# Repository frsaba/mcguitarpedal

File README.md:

# Teensy 4.1 Guitar Effects Pedal

#### Custom dual-layer PCB design:
- LM4562 based preamplifier stage with adjustable gain (1-20x) and 3-way attenuation switch for line-level compatibility
- 8+2+1 programmable buttons (up to 8 pushbuttons, 2 footswitches, 1 true bypass switch)
- 3 potentiometers (preamp gain + 2 programmable)
- 3 encoders (3 headers, but 2 are in use for now)
- 8 programmable LEDs
- 9V barrel jack input or USB power

[PCB design, front side](https://github.com/user-attachments/files/19494445/pcb_front.pdf)

[PCB design, back side](https://github.com/user-attachments/files/19494519/pcb_back.pdf)

## Hardware
- [Teensy 4.1](https://www.pjrc.com/store/teensy41.html)
- [Teensy Audio Adaptor board](https://www.pjrc.com/store/teensy3_audio.html)
- ILI9488 LCD panel (backlight brightness adjustable with PWM)

## Software

- C++ with PlatformIO
- [Teensy Audio Library](https://github.com/PaulStoffregen/Audio)
- UI made with [LVGL](https://lvgl.io)
- 5 implemented effects (more to come):
  - Chorus
  - Flanger
  - Tremolo
  - Delay
  - Reverb

Each effect can be separately toggled on/off and mixed with the dry/wet parameter. The effect parameters can be adjusted to tune the sound.

#### Misc. features
- Tuner mode
- Adjustable LED and display brightness
- Bypass switch
- Signal level feedback LED
- USB audio device for recording
- Headphone monitor out via Audio Board

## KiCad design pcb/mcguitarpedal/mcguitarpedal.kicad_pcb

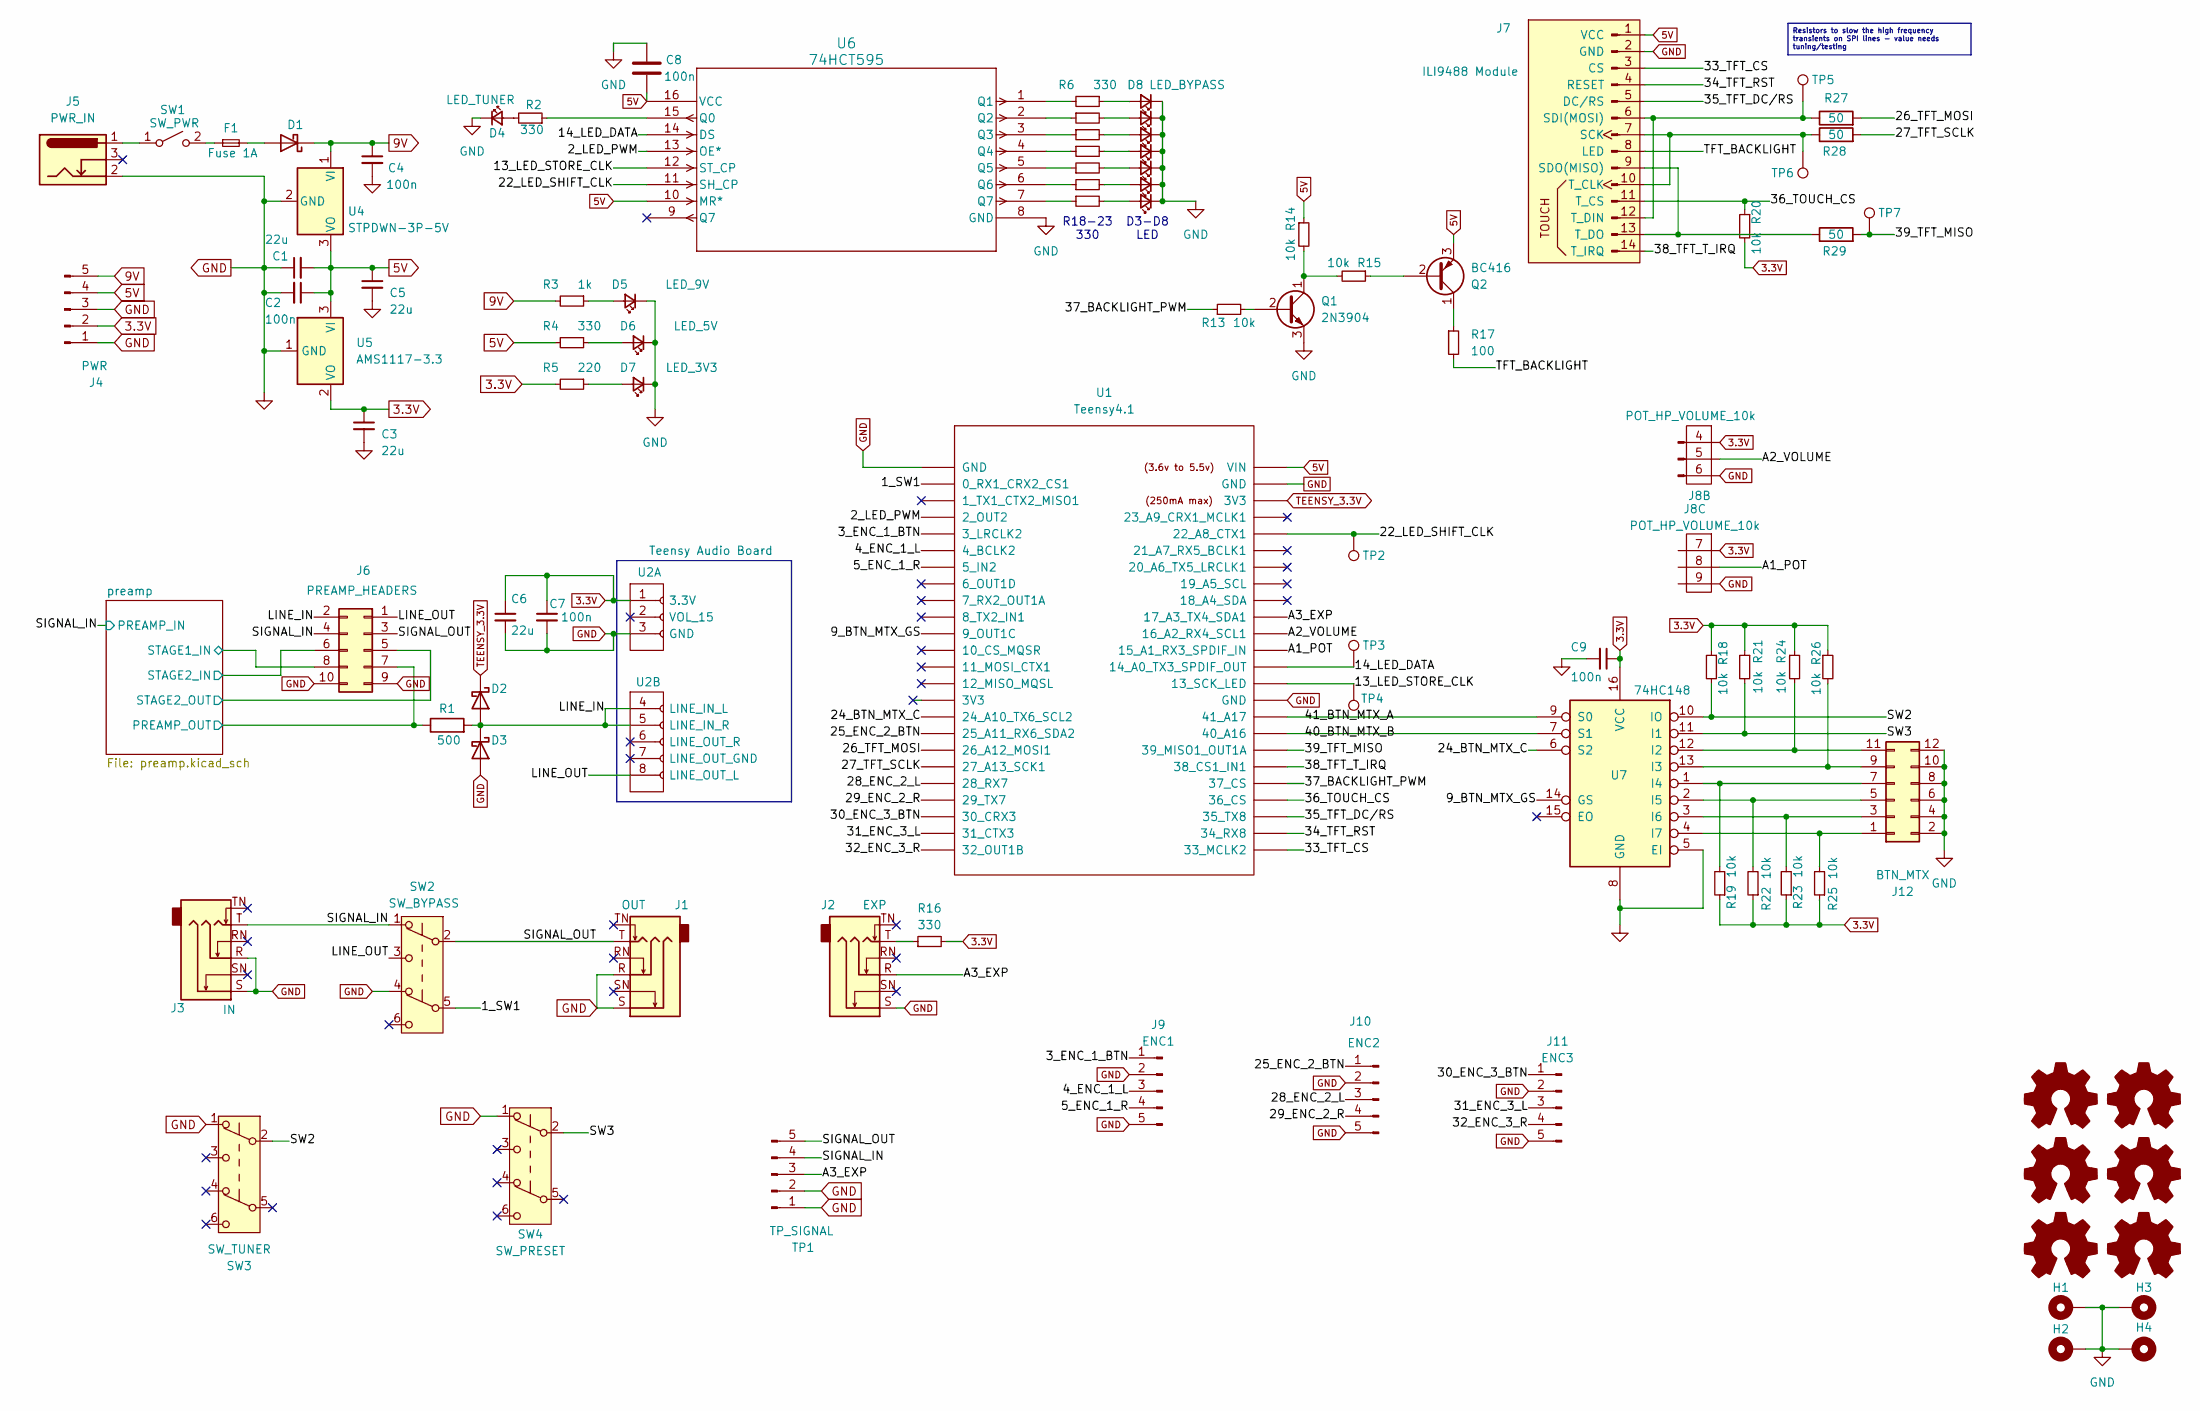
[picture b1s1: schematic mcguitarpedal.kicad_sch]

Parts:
C1, C3, C5, C6: 22u; CP_EIA-3216-18_Kemet-A_Pad1.58x1.35mm_HandSolder
C2, C4, C8, C9: 100n; C_1206_3216Metric_Pad1.33x1.80mm_HandSolder
C7: 100n; C_Rect_L7.2mm_W2.5mm_P5.00mm_FKS2_FKP2_MKS2_MKP2
D1, D2, D3: D_Schottky; D_DO-41_SOD81_P10.16mm_Horizontal
D4: LED_TUNER; LED_D5.0mm
D5: LED_9V; LED_D3.0mm
D6: LED_5V; LED_D3.0mm
D7: LED_3V3; LED_D3.0mm
D8: LED_BYPASS; LED_D5.0mm
D9: LED_STATUS; LED_D5.0mm
D10, D11, D12, D13, D14: LED; LED_D3.0mm
ENC1, ENC2, ENC3: Logo_Open_Hardware_Small; Floating Encoder
F1: Fuse 1A; Fuse_Littelfuse_395Series
H1, H2, H3, H4: MountingHole_Pad; MountingHole_2.2mm_M2_Pad
J1: OUT; Jack_6.35mm_Neutrik_NMJ6HCD2_Horizontal_3D_MODEL
J2: EXP; Jack_6.35mm_Neutrik_NMJ6HCD2_Horizontal_3D_MODEL
J3: IN; Jack_6.35mm_Neutrik_NMJ6HCD2_Horizontal_3D_MODEL
J4: PWR; PinHeader_1x05_P2.54mm_Vertical
J5: PWR_IN; BarrelJack_Kycon_KLDX-0202-xC_Horizontal
J6: PREAMP_HEADERS
J7: ILI9488 Module; ILI9488
J8: POT_HP_VOLUME_10k; POTS_HEADER
J9: ENC1; Encoder_headers
J10: ENC2; Encoder_headers
J11: ENC3; Encoder_headers
J12: BTN_MTX; PinHeader_2x06_P2.54mm_Vertical
POT1, POT2, POT3: Logo_Open_Hardware_Small; Floating Potentiometer
Q1: 2N3904; TO-92_Inline
Q2: BC416; TO-92_Inline
R1: 500; R_Axial_DIN0207_L6.3mm_D2.5mm_P7.62mm_Horizontal
R2, R4, R6, R7, R8, R9, R10, R11, R12, R16: 330; R_1206_3216Metric_Pad1.30x1.75mm_HandSolder
R3: 1k; R_Axial_DIN0207_L6.3mm_D2.5mm_P7.62mm_Horizontal
R5: 220; R_Axial_DIN0207_L6.3mm_D2.5mm_P7.62mm_Horizontal
R13, R14, R15, R18, R19, R20, R21, R22, R23, R24, R25, R26: 10k; R_1206_3216Metric_Pad1.30x1.75mm_HandSolder
R17: 100; R_Axial_DIN0207_L6.3mm_D2.5mm_P7.62mm_Horizontal
R27, R28, R29: 50; R_1206_3216Metric_Pad1.30x1.75mm_HandSolder
SW1: SW_PWR; PinHeader_1x02_P2.54mm_Vertical
SW2: SW_BYPASS; SW_PUSH_DPDT
SW3: SW_TUNER; SW_PUSH_DPDT
SW4: SW_PRESET; SW_PUSH_DPDT
TP1: TP_SIGNAL; PinHeader_1x05_P2.54mm_Vertical
TP2: SHIFT_CLK; TestPoint_Loop_D1.80mm_Drill1.0mm_Beaded
TP3: TP_LED_DATA; TestPoint_Loop_D1.80mm_Drill1.0mm_Beaded
TP4: TP_STORE_CLK; TestPoint_Loop_D1.80mm_Drill1.0mm_Beaded
TP5: TP_MOSI; TestPoint_Loop_D1.80mm_Drill1.0mm_Beaded
TP6: TP_SCLK; TestPoint_Loop_D1.80mm_Drill1.0mm_Beaded
TP7: TP_MISO; TestPoint_Loop_D1.80mm_Drill1.0mm_Beaded
U1: Teensy4.1; Teensy 4.1 with audio board
U2: Teensy Audio Board; 4.0audioshield
U4: STPDWN-3P-5V
U5: AMS1117-3.3; SOT-223-3_TabPin2
U6: 74HCT595; SOT109-1_NEX
U7: 74HC148; DIP16_300_TEX

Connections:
3.3V: C3.1, C6.1, C7.1, C9.1, J4.2, J8.4, J8.7, R5.2, R16.2, R18.1, R19.1, R20.2, R21.1, R22.1, R23.1, R24.1, R25.1, R26.1, U2.1 (3.3V), U5.2 (VO), U7.16 (VCC)
5V: C1.2, C2.1, C5.1, C8.2, J4.4, J7.1 (VCC), Q2.3 (E), R4.2, R14.1, U1.48 (VIN), U4.3 (VO), U5.3 (VI), U6.10 (MR*), U6.16 (VCC)
9V: C4.1, D1.1 (K), J4.5, R3.2, U4.1 (VI); also elsewhere on the board
/1_SW1: SW2.5 (B), U1.2 (0_RX1_CRX2_CS1)
/2_LED_PWM: U1.4 (2_OUT2), U6.13 (OE*)
/3_ENC_1_BTN: J9.1, U1.5 (3_LRCLK2)
/4_ENC_1_L: J9.3, U1.6 (4_BCLK2)
/5_ENC_1_R: J9.4, U1.7 (5_IN2)
/9_BTN_MTX_GS: U1.11 (9_OUT1C), U7.14 (GS)
/13_LED_STORE_CLK: TP4.1, U1.35 (13_SCK_LED), U6.12 (ST_CP)
/14_LED_DATA: TP3.1, U1.36 (14_A0_TX3_SPDIF_OUT), U6.14 (DS)
/22_LED_SHIFT_CLK: TP2.1, U1.44 (22_A8_CTX1), U6.11 (SH_CP)
/24_BTN_MTX_C: U1.16 (24_A10_TX6_SCL2), U7.6 (S2)
/25_ENC_2_BTN: J10.1, U1.17 (25_A11_RX6_SDA2)
/26_TFT_MOSI: R27.2, U1.18 (26_A12_MOSI1)
/27_TFT_SCLK: R28.2, U1.19 (27_A13_SCK1)
/28_ENC_2_L: J10.3, U1.20 (28_RX7)
/29_ENC_2_R: J10.4, U1.21 (29_TX7)
/30_ENC_3_BTN: J11.1, U1.22 (30_CRX3)
/31_ENC_3_L: J11.3, U1.23 (31_CTX3)
/32_ENC_3_R: J11.4, U1.24 (32_OUT1B)
/33_TFT_CS: J7.3 (CS), U1.25 (33_MCLK2)
/34_TFT_RST: J7.4 (RESET), U1.26 (34_RX8)
/35_TFT_DC/RS: J7.5 (DC/RS), U1.27 (35_TX8)
/36_TOUCH_CS: J7.11 (T_CS), R20.1, U1.28 (36_CS)
/37_BACKLIGHT_PWM: R13.1, U1.29 (37_CS)
/38_TFT_T_IRQ: J7.14 (T_IRQ), U1.30 (38_CS1_IN1)
/39_TFT_MISO: R29.2, TP7.1, U1.31 (39_MISO1_OUT1A)
/40_BTN_MTX_B: U1.32 (40_A16), U7.7 (S1)
/41_BTN_MTX_A: U1.33 (41_A17), U7.9 (S0)
/A1_POT: J8.8, U1.37 (15_A1_RX3_SPDIF_IN)
/A2_VOLUME: J8.5, U1.38 (16_A2_RX4_SCL1)
/A3_EXP: J2.R, TP1.3, U1.39 (17_A3_TX4_SDA1)
/LINE_IN: D2.2 (A), D3.1 (K), J6.2, R1.2, U2.4 (LINE_IN_L), U2.5 (LINE_IN_R)
/LINE_OUT: J6.1, SW2.3 (C), U2.8 (LINE_OUT_L)
/SIGNAL_IN: J3.T, J6.4, SW2.1 (A), TP1.4; also elsewhere on the board
/SIGNAL_OUT: J1.T, J6.3, SW2.2 (B), TP1.5
/SW2: R18.2, SW3.2 (B), U7.10 (IO)
/SW3: R21.2, SW4.2 (B), U7.11 (I1)
/TFT_BACKLIGHT: J7.8 (LED), R17.2
/preamp/PREAMP_OUT: J6.7, R1.1; also elsewhere on the board
/preamp/STAGE1_IN: J6.8; also elsewhere on the board
/preamp/STAGE2_IN: J6.6; also elsewhere on the board
/preamp/STAGE2_OUT: J6.5; also elsewhere on the board
GND: C1.1, C2.2, C3.2, C4.2, C5.2, C6.2, C7.2, C8.1, C9.2, D3.2 (A), D4.1 (K), D5.1 (K), D6.1 (K), D7.1 (K), D8.1 (K), D9.1 (K), D10.1 (K), D11.1 (K), D12.1 (K), D13.1 (K), D14.1 (K), H1.1, H2.1, H3.1, H4.1, J1.R, J1.S, J2.S, J3.R, J3.S, J4.1, J4.3, J5.2, J6.9, J6.10, J7.2 (GND), J8.6, J8.9, J9.2, J9.5, J10.2, J10.5, J11.2, J11.5, J12.2, J12.4, J12.6, J12.8, J12.10, J12.12, Q1.3 (E), SW2.4 (A), SW3.1 (A), SW4.1 (A), TP1.1, TP1.2, U1.1 (GND), U1.34 (GND), U1.47 (GND), U2.3 (GND), U4.2 (GND), U5.1 (GND), U6.8 (GND), U7.5 (EI), U7.8 (GND); also elsewhere on the board
unnamed: D1.2 (A), F1.2
unnamed: D4.2 (A), R2.2
unnamed: D5.2 (A), R3.1
unnamed: D6.2 (A), R4.1
unnamed: D7.2 (A), R5.1
unnamed: D8.2 (A), R6.1
unnamed: D9.2 (A), R7.2
unnamed: D10.2 (A), R8.2
unnamed: D11.2 (A), R9.2
unnamed: D12.2 (A), R10.2
unnamed: D13.2 (A), R11.2
unnamed: D14.2 (A), R12.2
unnamed: J2.T, R16.1
unnamed: J7.7 (SCK), J7.10 (T_CLK), R28.1, TP6.1
unnamed: J7.6 (SDI(MOSI)), J7.12 (T_DIN), R27.1, TP5.1
unnamed: J7.9 (SDO(MISO)), J7.13 (T_DO), R29.1
unnamed: J12.1, R25.2, U7.4 (I7)
unnamed: J12.3, R23.2, U7.3 (I6)
unnamed: J12.5, R22.2, U7.2 (I5)
unnamed: J12.7, R19.2, U7.1 (I4)
unnamed: J12.9, R26.2, U7.13 (I3)
unnamed: J12.11, R24.2, U7.12 (I2)
unnamed: Q1.2 (B), R13.2
unnamed: Q1.1 (C), R14.2, R15.2
unnamed: Q2.2 (B), R15.1
unnamed: Q2.1 (C), R17.1
unnamed: R12.1, U6.7 (Q7)
unnamed: J5.1, SW1.1 (A)
unnamed: F1.1, SW1.2 (B)
unnamed: R2.1, U6.15 (Q0)
unnamed: R6.2, U6.1 (Q1)
unnamed: R7.1, U6.2 (Q2)
unnamed: R8.1, U6.3 (Q3)
unnamed: R9.1, U6.4 (Q4)
unnamed: R10.1, U6.5 (Q5)
unnamed: R11.1, U6.6 (Q6)
TEENSY_3.3V: D2.1 (K), U1.46 (3V3); also elsewhere on the board

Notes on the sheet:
Resistors to slow the high frequency transients on SPI lines - value needs tuning/testing
D3-D8 LED
R18-23 330

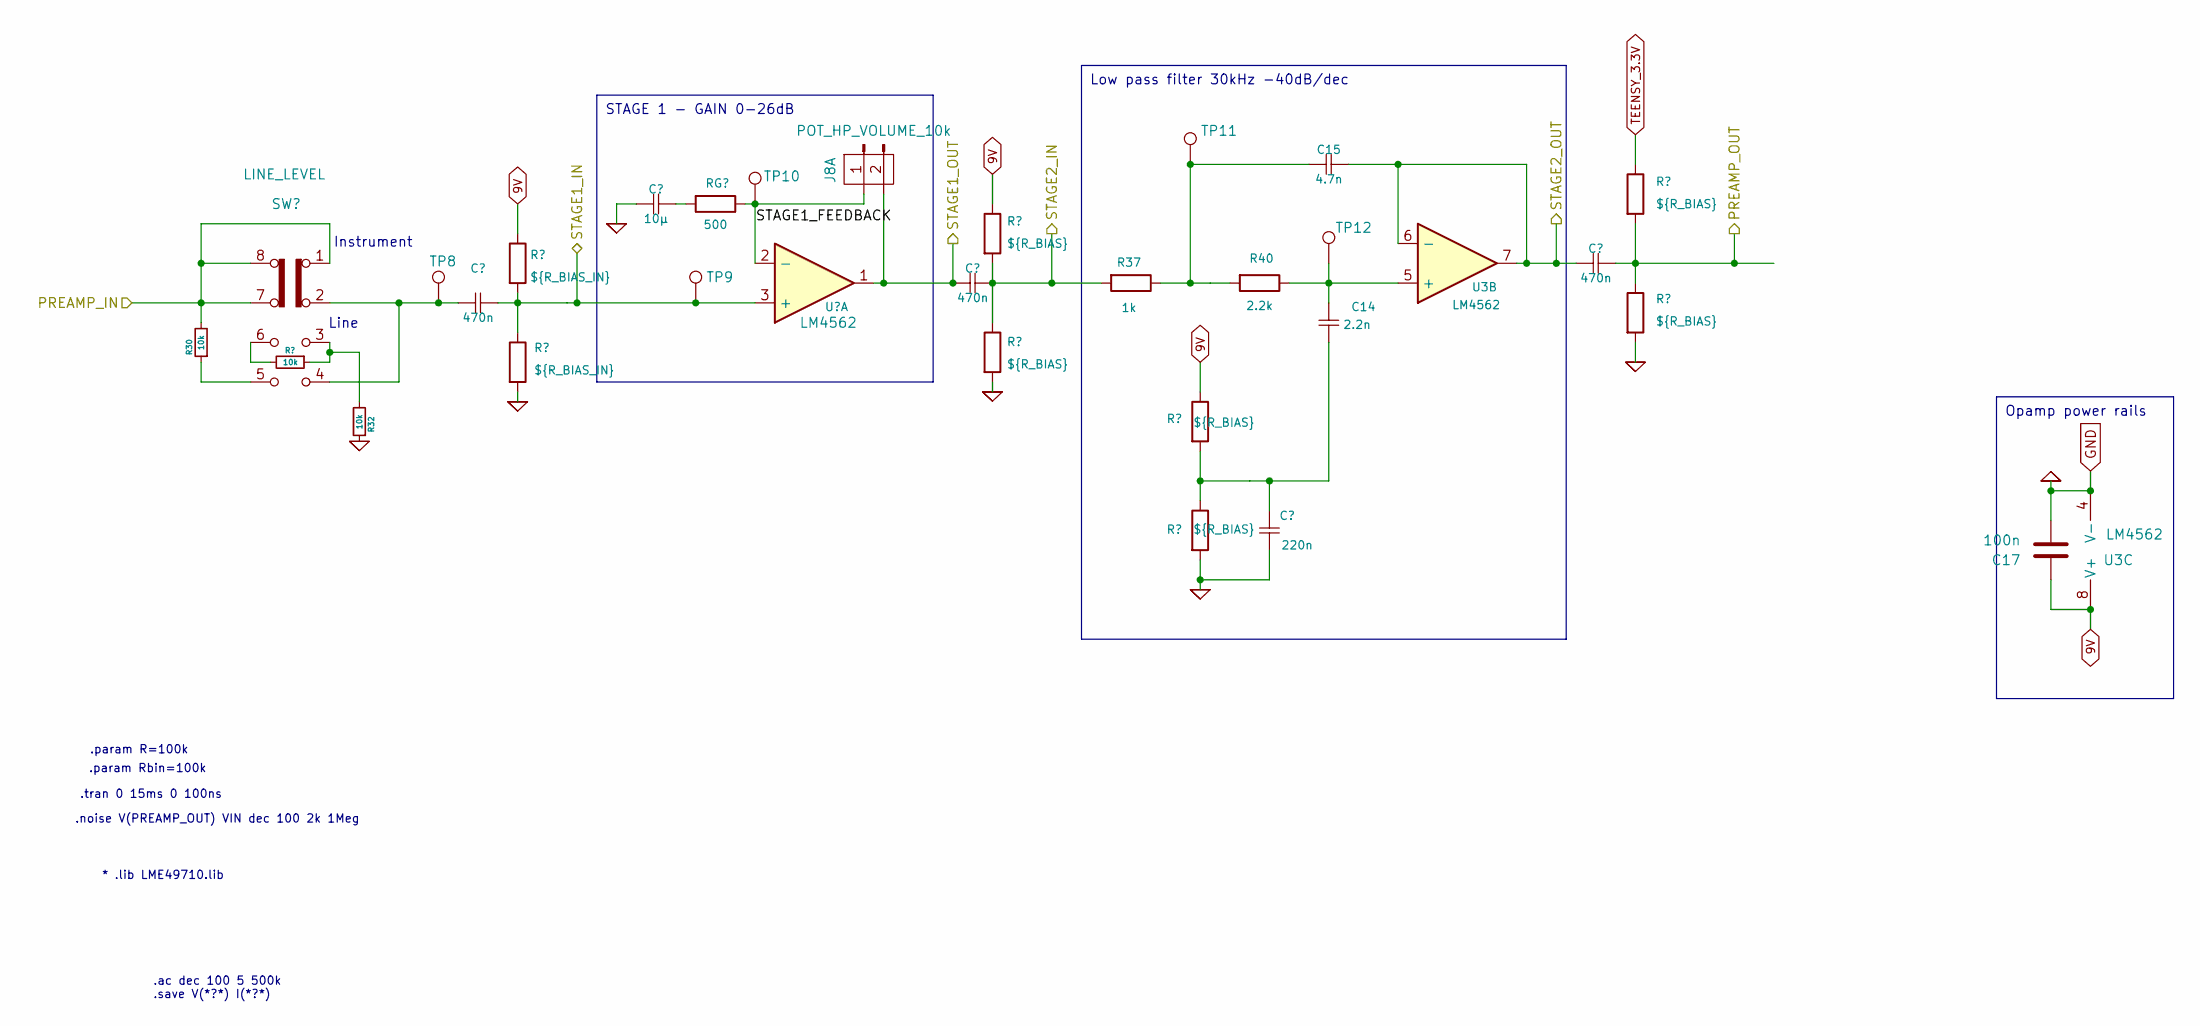
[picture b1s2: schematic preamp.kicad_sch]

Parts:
C10, C12, C16: 470n; C_Rect_L7.2mm_W3.5mm_P5.00mm_FKS2_FKP2_MKS2_MKP2
C11: 10µ; CP_Radial_D6.3mm_P2.50mm
C13: 220n; C_Rect_L7.2mm_W2.5mm_P5.00mm_FKS2_FKP2_MKS2_MKP2
C14: 2.2n; C_Rect_L7.5mm_W6.5mm_P5.00mm
C15: 4.7n; C_Rect_L7.2mm_W7.2mm_P5.00mm_FKS2_FKP2_MKS2_MKP2
C17: 100n; C_1206_3216Metric_Pad1.33x1.80mm_HandSolder
J8: POT_HP_VOLUME_10k; POTS_HEADER
R30, R31, R32: 10k; R_1206_3216Metric_Pad1.30x1.75mm_HandSolder
R33, R34: ${R_BIAS_IN}; R_Axial_DIN0207_L6.3mm_D2.5mm_P7.62mm_Horizontal
R35, R36, R38, R39, R41, R42: ${R_BIAS}; R_Axial_DIN0207_L6.3mm_D2.5mm_P7.62mm_Horizontal
R37: 1k; R_Axial_DIN0207_L6.3mm_D2.5mm_P7.62mm_Horizontal
R40: 2.2k; R_Axial_DIN0207_L6.3mm_D2.5mm_P7.62mm_Horizontal
RG1: 500; R_Axial_DIN0207_L6.3mm_D2.5mm_P7.62mm_Horizontal
SW5: LINE_LEVEL; DP3T slide switch
TP8, TP9, TP10, TP11, TP12: TestPoint; TestPoint_Loop_D1.80mm_Drill1.0mm_Beaded
U3: LM4562; lm4562

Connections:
9V: C17.1, R33.1, R35.1, R38.1, U3.8 (V+); also elsewhere on the board
/SIGNAL_IN: R30.2, SW5.1 (A), SW5.7 (B), SW5.8 (C); also elsewhere on the board
/preamp/PREAMP_OUT: C16.1, R41.2, R42.1; also elsewhere on the board
/preamp/STAGE1_FEEDBACK: J8.1, RG1.1, TP10.1, U3.2 (-)
/preamp/STAGE1_IN: C10.1, R33.2, R34.1, TP9.1, U3.3 (+); also elsewhere on the board
/preamp/STAGE1_OUT: C12.2, J8.2, U3.1
/preamp/STAGE2_IN: C12.1, R35.2, R36.1, R37.2; also elsewhere on the board
/preamp/STAGE2_OUT: C15.1, C16.2, U3.6 (-), U3.7; also elsewhere on the board
GND: C11.2, C13.2, C17.2, R32.1, R34.2, R36.2, R39.2, R42.2, U3.4 (V-); also elsewhere on the board
unnamed: C11.1, RG1.2
unnamed: C13.1, C14.2, R38.2, R39.1
unnamed: C15.2, R37.1, R40.2, TP11.1
unnamed: R30.1, SW5.5
unnamed: R31.1, R32.2, SW5.3 (C)
unnamed: R31.2, SW5.6 (A)
unnamed: C10.2, SW5.2 (B), SW5.4 (D), TP8.1
unnamed: C14.1, R40.1, TP12.1, U3.5 (+)
TEENSY_3.3V: R41.1; also elsewhere on the board

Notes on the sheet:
Opamp power rails
Low pass filter 30kHz -40dB/dec
STAGE 1 - GAIN 0-26dB
Line
Instrument
.param R=100k
.noise V(PREAMP_OUT) VIN dec 100 2k 1Meg
.param Rbin=100k
* .lib LME49710.lib
.ac dec 100 5 500k .save V(*?*) I(*?*)
.tran 0 15ms 0 100ns

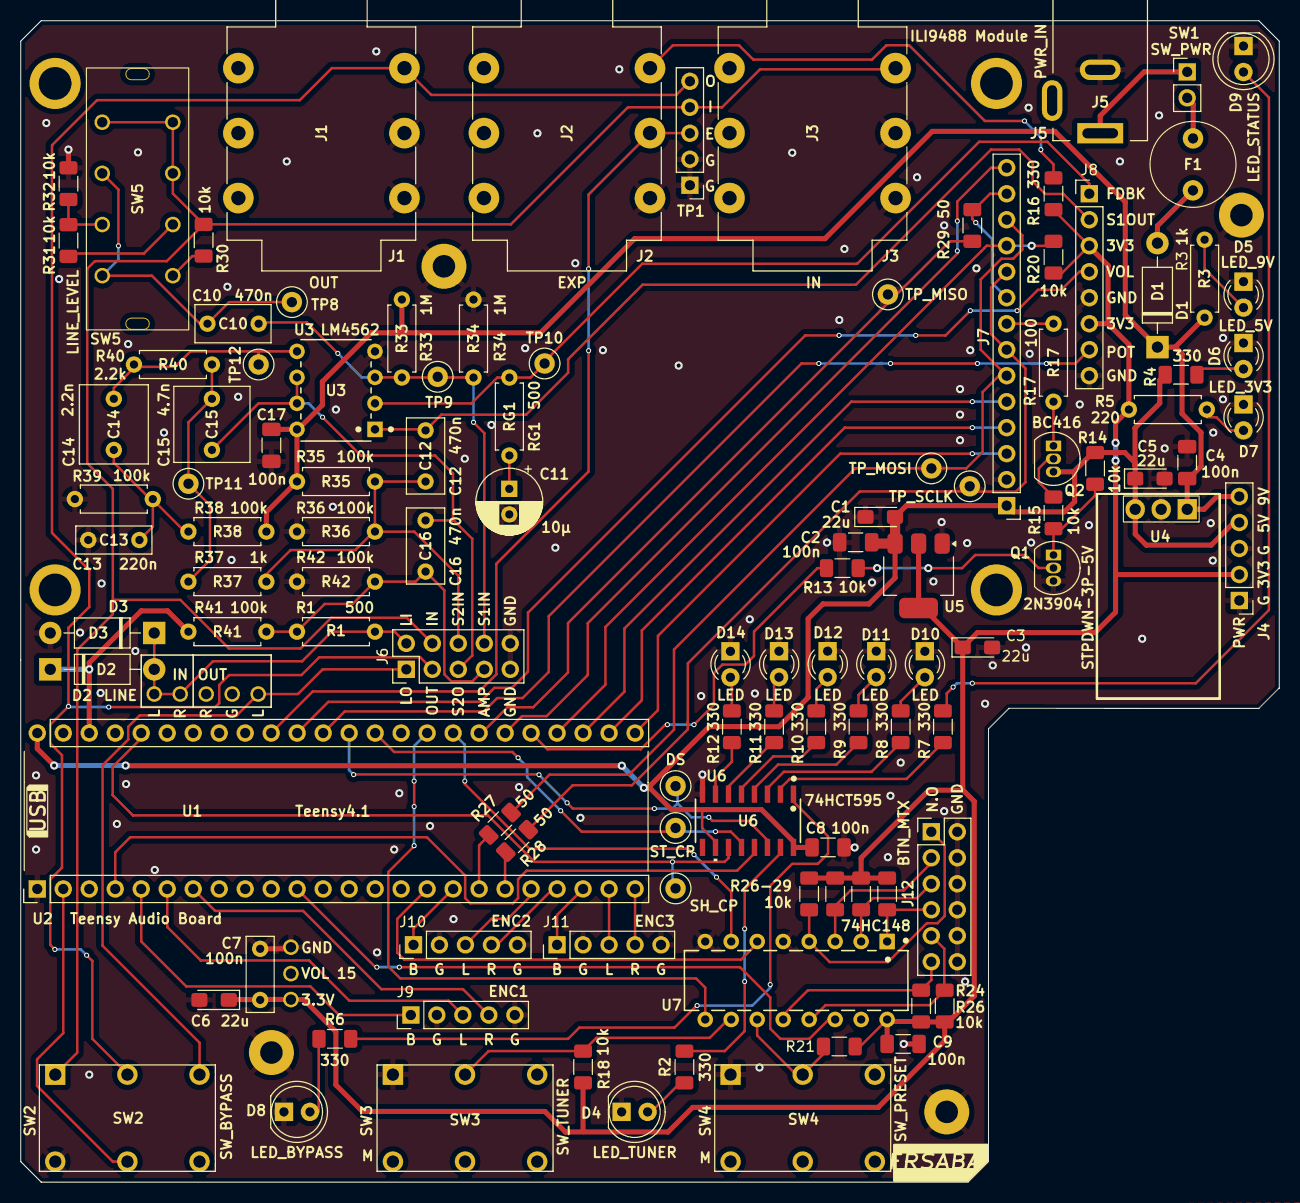
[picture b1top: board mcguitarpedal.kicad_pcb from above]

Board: 2 copper layers, 123.0 x 113.5 mm, 123 parts (0 on the bottom side), 92 nets.

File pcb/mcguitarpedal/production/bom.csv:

Designator,Footprint,Quantity,Value,LCSC Part #
"C1, C3, C5, C6",CP_EIA-3216-18_Kemet-A_Pad1.58x1.35mm_HandSolder,4,22u,
"C10, C12, C16",C_Rect_L7.2mm_W3.5mm_P5.00mm_FKS2_FKP2_MKS2_MKP2,3,470n,
C11,CP_Radial_D6.3mm_P2.50mm,1,10µ,
C13,C_Rect_L7.2mm_W2.5mm_P5.00mm_FKS2_FKP2_MKS2_MKP2,1,220n,
C14,C_Rect_L7.5mm_W6.5mm_P5.00mm,1,2.2n,
C15,C_Rect_L7.2mm_W7.2mm_P5.00mm_FKS2_FKP2_MKS2_MKP2,1,4.7n,
"C17, C2, C4, C8, C9",1206,5,100n,
C7,C_Rect_L7.2mm_W2.5mm_P5.00mm_FKS2_FKP2_MKS2_MKP2,1,100n,
"D1, D2, D3",D_DO-41_SOD81_P10.16mm_Horizontal,3,D_Schottky,
"D10, D11, D12, D13, D14",LED_D3.0mm,5,LED,
D4,LED_D5.0mm,1,LED_TUNER,
D5,LED_D3.0mm,1,LED_9V,
D6,LED_D3.0mm,1,LED_5V,
D7,LED_D3.0mm,1,LED_3V3,
D8,LED_D5.0mm,1,LED_BYPASS,
D9,LED_D5.0mm,1,LED_STATUS,
F1,Fuse_Littelfuse_395Series,1,Fuse 1A,
J1,Jack_6.35mm_Neutrik_NMJ6HCD2_Horizontal_3D_MODEL,1,OUT,
J10,Encoder_headers,1,ENC2,
J11,Encoder_headers,1,ENC3,
J12,PinHeader_2x06_P2.54mm_Vertical,1,BTN_MTX,
J2,Jack_6.35mm_Neutrik_NMJ6HCD2_Horizontal_3D_MODEL,1,EXP,
J3,Jack_6.35mm_Neutrik_NMJ6HCD2_Horizontal_3D_MODEL,1,IN,
J4,PinHeader_1x05_P2.54mm_Vertical,1,PWR,
J5,BarrelJack_Kycon_KLDX-0202-xC_Horizontal,1,PWR_IN,
J6,PREAMP_HEADERS,1,PREAMP_HEADERS,
J7,ILI9488,1,ILI9488 Module,
J8,POTS_HEADER,1,POT_HP_VOLUME_10k,
J9,Encoder_headers,1,ENC1,
Q1,TO-92_Inline,1,2N3904,
Q2,TO-92_Inline,1,BC416,
"R1, RG1",R_Axial_DIN0207_L6.3mm_D2.5mm_P7.62mm_Horizontal,2,500,
"R10, R11, R12, R16, R2, R4, R6, R7, R8, R9",1206,10,330,
"R13, R14, R15, R18, R19, R20, R21, R22, R23, R24, R25, R26, R30, R31, R32",1206,15,10k,
R17,R_Axial_DIN0207_L6.3mm_D2.5mm_P7.62mm_Horizontal,1,100,
"R27, R28, R29",1206,3,50,
"R3, R37",R_Axial_DIN0207_L6.3mm_D2.5mm_P7.62mm_Horizontal,2,1k,
"R33, R34",R_Axial_DIN0207_L6.3mm_D2.5mm_P7.62mm_Horizontal,2,1M,
"R35, R36, R38, R39, R41, R42",R_Axial_DIN0207_L6.3mm_D2.5mm_P7.62mm_Horizontal,6,100k,
R40,R_Axial_DIN0207_L6.3mm_D2.5mm_P7.62mm_Horizontal,1,2.2k,
R5,R_Axial_DIN0207_L6.3mm_D2.5mm_P7.62mm_Horizontal,1,220,
SW1,PinHeader_1x02_P2.54mm_Vertical,1,SW_PWR,
SW2,SW_PUSH_DPDT,1,SW_BYPASS,
SW3,SW_PUSH_DPDT,1,SW_TUNER,
SW4,SW_PUSH_DPDT,1,SW_PRESET,
SW5,DP3T slide switch,1,LINE_LEVEL,
TP1,PinHeader_1x05_P2.54mm_Vertical,1,TP_SIGNAL,
"TP10, TP11, TP12, TP8, TP9",TestPoint_Loop_D1.80mm_Drill1.0mm_Beaded,5,TestPoint,
TP2,TestPoint_Loop_D1.80mm_Drill1.0mm_Beaded,1,SHIFT_CLK,
TP3,TestPoint_Loop_D1.80mm_Drill1.0mm_Beaded,1,TP_LED_DATA,
TP4,TestPoint_Loop_D1.80mm_Drill1.0mm_Beaded,1,TP_STORE_CLK,
TP5,TestPoint_Loop_D1.80mm_Drill1.0mm_Beaded,1,TP_MOSI,
TP6,TestPoint_Loop_D1.80mm_Drill1.0mm_Beaded,1,TP_SCLK,
TP7,TestPoint_Loop_D1.80mm_Drill1.0mm_Beaded,1,TP_MISO,
U1,Teensy 4.1 with audio board,1,Teensy4.1,
U2,4.0audioshield,1,Teensy Audio Board,
U3,lm4562,1,LM4562,
U4,STPDWN-3P-5V,1,STPDWN-3P-5V,
U5,SOT-223-3_TabPin2,1,AMS1117-3.3,
U6,SOT109-1_NEX,1,74HCT595,
U7,DIP16_300_TEX,1,74HC148,

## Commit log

2024-03-11 Delay and reverb with encoders
2024-03-21 Add adcHighPassFilterDisable
2024-03-25 TFT test with audio library running
2024-03-29 Param, Effect and Delay
2024-04-04 Write param selection to display
2024-04-08 Button test
2024-04-08 Reverb
2024-05-03 Dry/wet param
2024-05-03 Updated preamp schematic
2024-05-20 Param default constructor
2024-05-20 Manual wiring for dry/wet mixer
2024-05-20 TODO comments
2024-05-20 Tremolo effect
2024-06-02 Effects folder
2024-06-20 Flanger code
2024-06-20 Move to TFT_eSPI
2024-06-27 LVGL migration
2024-06-29 Lists side by side
2024-06-29 Effects list creation
2024-06-30 File associations
2024-06-30 Effects and menu navigation, bypass event
2024-07-05 Create arc function
2024-07-09 Param arc
2024-07-09 Change param value labels and arcs
2024-07-16 Param unit string
2024-07-19 Unit string, two encoder navigation
2024-07-23 Serialization test
2024-07-24 Fixed color byte order
2024-07-29 Save preset v1
2024-07-29 Navigate preset list
2024-08-05 Save presets function
2024-08-10 Save 1 preset
2024-08-10 Moved display code to /interface folder
2024-08-10 Moved code from display.cpp to input_events.cpp
2024-08-10 Load presets function
2024-08-12 apply_preset_values function
2024-08-12 Optional serialize to EEPROM
2024-08-12 update_value_label and update_arc helpers
2024-08-13 Apply params to knobs
2024-08-30 Adjusted pinout
2024-08-30 Save/load active preset
2024-09-06 Preamp filter design
2024-09-08 Non-inverting experiment
2024-09-11 Non-inverting design
2024-09-15 Tuned non-inverting preamp schematic
2024-09-15 Fixed loading active preset
2024-09-29 Kicad preamp schematic
2024-09-30 Teensy symbol libraries
2024-10-06 Revised pinout
2024-10-08 Schematic symbols
2024-10-08 4094 wiring
2024-10-12 ILI9488 schematic
2024-10-12 PCB physical layout
2024-10-13 Basic PCB routing
2024-10-13 Mostly routed board
2024-10-13 Reorganized power section
2024-10-14 Encoder headers
2024-10-15 Changed to DPDT switches
2024-10-16 Rearranged preamp circuit
2024-10-16 Input protection
2024-10-20 HCT595, audio shield sockets
2024-10-20 Miniaturization
2024-10-20 Reorganized power traces
2024-10-21 Routing additonal power
2024-10-22 Display backlight control schematic
2024-10-23 Backlight control, PWR leds
2024-10-24 Final encoder and display pinout
2024-10-24 Rearranged pullups
2024-10-25 Silkscreen labeling
2024-10-28 Final 1.0 design
2024-11-12 Display rotation
2024-11-17 Encoder shroud mechanical design
2024-11-17 Updated .gitignore
2024-11-18 LED test
2024-11-19 Encoder shroud V2
2024-11-19 Redesigned shroud mounting
2024-11-22 LED definitions
2024-11-23 Button decoder test
2024-11-23 Move serialization functions to flash
2024-11-26 Shroud v2
2024-11-27 Feedback delay
2024-11-27 Auxillary button holes
2024-11-29 Shroud V3
2024-11-29 Button decoder logic
2024-11-29 Load prev/next preset
2024-11-30 Status bar, custom icons test
2024-11-30 Headphone volume and mix
2024-11-30 Preset leds
2024-11-30 Screen styling
2024-12-01 Basic tuner mode
2024-12-01 Patch cords vector
2024-12-01 Flanger v1
2024-12-01 Effects tuning
2024-12-02 Save preset fixes
2024-12-02 Changed reverb to freeverb
2024-12-03 Param icons
2024-12-03 Icons for all params
2024-12-03 Fixed initial preset number display
2024-12-05 Show active effects using LEDS
2024-12-07 USB audio
2024-12-08 Front plate design 4
2024-12-09 Front cover plate
2024-12-10 Bypass LED, adcHighPassFilterDisable
2024-12-10 snapshot experiment
2024-12-14 Bypass blink
2024-12-14 Missing models, PCB pdf exports
2024-12-22 Brightness settings
2024-12-23 Threshold settings
2025-01-02 Case sensitive includes
2025-03-27 Added readme description
2025-03-27 Added additional pictures to readme
